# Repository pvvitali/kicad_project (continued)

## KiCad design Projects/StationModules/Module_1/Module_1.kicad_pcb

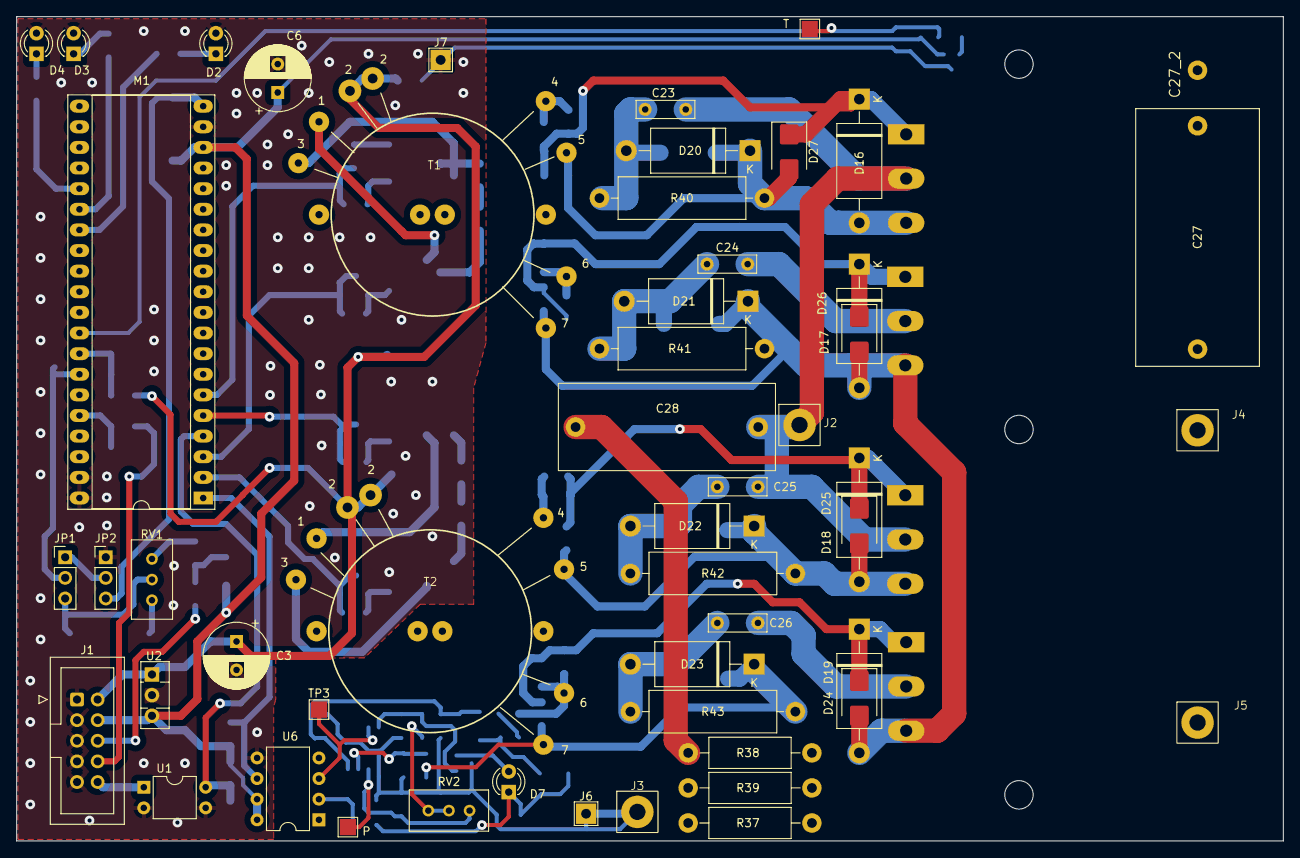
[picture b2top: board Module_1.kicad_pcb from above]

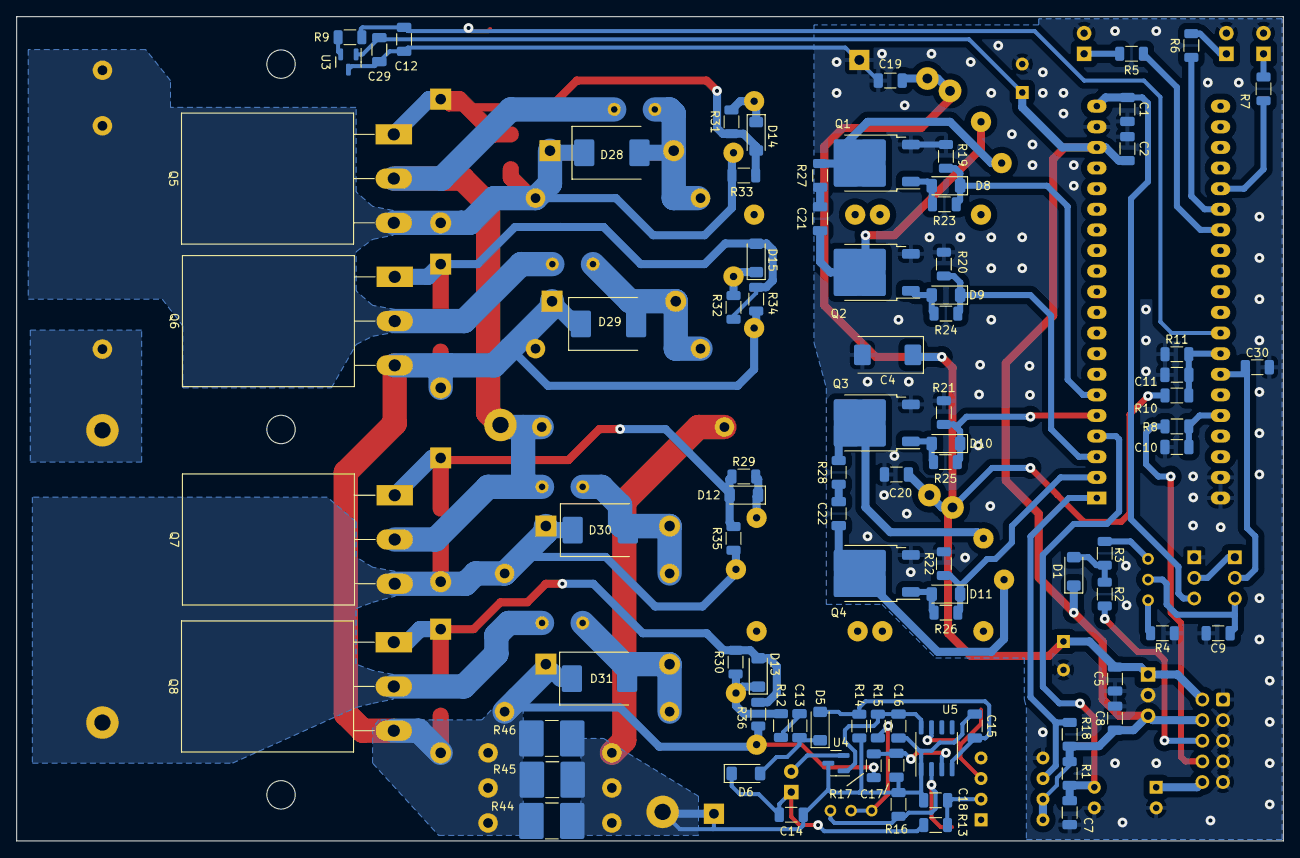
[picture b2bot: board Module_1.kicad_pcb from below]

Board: 2 copper layers, 156.0 x 101.5 mm, 142 parts (87 on the bottom side), 68 nets.

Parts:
C1, C2, C5, C7, C8, C11, C12, C16, C18, C29, C30: 0,1uF; C_1206_3216Metric
C3, C6: 470uF 25V; CP_Radial_D8.0mm_P3.50mm
C4: 100uF; CP_EIA-7343-15_Kemet-W
C9, C10: 10nF; C_1206_3216Metric
C13, C14, C15: 0,33uF; C_1206_3216Metric
C17: 2,2n; C_1206_3216Metric
C19, C20: 0,47uF; C_1206_3216Metric
C21, C22: 1n; C_1206_3216Metric
C23, C24, C25, C26: 1n 630v; C_Rect_L7.0mm_W2.0mm_P5.00mm
C27: 2u 600V; C_Rect_L31.5mm_W15.0mm_P27.50mm_MKS4
C27_2: (no value)
C28: 0,47u 600V; C_Rect_L26.5mm_W10.5mm_P22.50mm_MKS4
D1, D5, D6, D8, D9, D10, D11, D12, D13, D14, D15: LL4148; D_MiniMELF
D2, D3, D4, D7: LED_D3.0mm
D16, D17, D18, D19: P6KE18CA; D_DO-201AE_P15.24mm_Horizontal
D20, D21, D22, D23: UF5408; D_DO-201AE_P15.24mm_Horizontal
D24, D25, D26, D27: SMBJ18CA; D_SMB
D28, D29, D30, D31: ES3JC; D_SMC
H1, H2, H3: MountingHole; MountingHole_3.5mm
J1: IDC-Header_2x05_P2.54mm_Vertical
J2: +310; PinD2mm
J3: -310; PinD2mm
J4: PowerTrans1; PinD2mm
J5: PowerTrans2; PinD2mm
J6: -310V; TestPoint_THTPad_2.5x2.5mm_Drill1.2mm
J7: -12V; TestPoint_THTPad_2.5x2.5mm_Drill1.2mm
JP1, JP2: Jumper_3_Open; PinHeader_1x03_P2.54mm_Vertical
M1: BluePillStm32; DIP-40_W15.24mm_Socket_LongPads
P: TestPoint; TestPoint_Pad_2.0x2.0mm
Q1, Q2, Q3, Q4: STD20NF06T4; TO-252-2
Q5, Q6, Q7, Q8: STW20NM60; TO-247-3_Horizontal_TabUp
R1, R3, R4, R9, R11, R15: 4,7k; R_1206_3216Metric
R2: 470; R_1206_3216Metric
R5, R6, R7, R13, R27, R28: 330; R_1206_3216Metric
R8: 100; R_1206_3216Metric
R10: 15k; R_1206_3216Metric
R12: 680; R_1206_3216Metric
R14, R18: 1,5k; R_1206_3216Metric
R16: 150; R_1206_3216Metric
R17: 1k; R_1206_3216Metric
R19, R20, R21, R22: 3,3k; R_1206_3216Metric
R23, R24, R25, R26, R29, R30, R31, R32: 75; R_1206_3216Metric
R33, R34, R35, R36: 2,2k; R_1206_3216Metric
R37, R38, R39: 0,01; R_Axial_DIN0411_L9.9mm_D3.6mm_P15.24mm_Horizontal
R40, R41, R42, R43: 18; R_Axial_DIN0516_L15.5mm_D5.0mm_P20.32mm_Horizontal
R44, R45, R46: 0,01; R_2816_7142Metric
RV1, RV2: 5k; Potentiometer_Bourns_3296W_Vertical
T: TestPoint; TestPoint_Pad_2.0x2.0mm
T1, T2: Transformer_SP_2S; Trans_SP_2S
TP3: TestPoint; TestPoint_Pad_2.0x2.0mm
U1: PC817; DIP-4_W7.62mm
U2: L7805; TO-126-3_Vertical
U3: TC1047AxNB; SOT-23
U4: 78L05S; SOT-23
U5: LM311; SO-8_3.9x4.9mm_P1.27mm
U6: 6N137; DIP-8_W7.62mm

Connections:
+3V3: C1.1, JP2.3 (B), M1.20 (3V3)
+5V: C2.1, C6.1, C8.1, C29.1, D1.1 (K), J1.4, M1.18 (5V), R1.2, R18.2, U2.3 (OUT), U3.1 (V_{DD}), U6.7 (EN), U6.8 (VCC)
+12V: C3.1, C4.1, C5.1, C19.2, C20.2, J1.2, R10.2, T1.2 (PM), T2.2 (PM), U2.1 (IN)
/DriverFet/Driver_A: Q1.2 (D), R27.2, T1.3 (IN-)
/DriverFet/Driver_AN: C21.2, Q2.2 (D), T1.1 (IN+)
/DriverFet/Driver_B: Q3.2 (D), R28.2, T2.1 (IN+)
/DriverFet/Driver_BN: C22.2, Q4.2 (D), T2.3 (IN-)
/IN1: J1.10, U1.1
/IN_1: C7.1, M1.4 (PB15/SPI2_MOSI), R1.1, U1.4
/I_ER: M1.1 (PB12/SPI2_NSS), R18.1, U6.6 (VO)
/LED1: M1.25 (PA0), R7.1
/LED2: M1.26 (PA1), R6.1
/LED3: M1.27 (PA2/USART2_TX), R5.1
/OS: C30.1, JP1.2 (C), M1.34 (PB1)
/OS_IN: J1.6, R2.1
/OUTI1: J1.8, R8.1
/OUT_1: C10.1, M1.36 (PB11/USART3_RX), R8.2
/PWM_A: D8.1 (K), M1.6 (PA9/USART1_TX), R19.2, R23.2
/PWM_AN: D9.1 (K), M1.3 (PB14/SPI2_MISO), R20.1, R24.2
/PWM_B: D10.1 (K), M1.5 (PA8), R21.2, R25.2
/PWM_BN: D11.1 (K), M1.2 (PB13/SPI2_SCK), R22.1, R26.2
/Shunt+: D17.2 (A2), D19.2 (A2), D21.1 (A1), D23.1 (A1), D24.2 (A2), D26.2 (A2), D29.1 (K), D31.1 (K), Q6.3 (S), Q8.3 (S), R17.2, R34.1, R36.1, R37.1, R38.1, R39.1, R41.2, R43.2, R44.1, R45.1, R46.1, T1.7 (OUT2B), T2.7 (OUT2B)
/Shunt-: C14.2, C15.1, C16.2, C17.2, C18.2, C28.2, J3.1, J6.1, R14.2, R16.1, R37.2, R38.2, R39.2, R44.2, R45.2, R46.2, U4.3 (GND), U5.1 (GND)
/TMP: C12.1, M1.32 (PA7/SPI_MOSI), R9.2, T.1
/Transf_out: D13.1 (K), R12.2, R30.2, T2.6 (OUT2A)
/UP: C11.1, M1.33 (PB0), R10.1, R11.2
GND: C1.2, C2.2, C3.2, C4.2, C5.2, C6.2, C7.2, C8.2, C9.2, C10.2, C11.2, C12.2, C19.1, C20.1, C29.2, C30.2, D2.2 (K), D3.2 (K), D4.2 (K), J1.1, J1.3, J1.5, J1.7, J1.9, J7.1, JP2.1 (A), M1.19 (GND), M1.39 (GND), M1.40 (GND), Q1.3 (S), Q2.3 (S), Q3.3 (S), Q4.3 (S), R4.1, R11.1, R19.1, R20.2, R21.1, R22.2, U1.2, U1.3, U2.2 (GND), U3.3 (GND), U6.5 (GND)
unnamed: C13.1, R12.1
unnamed: C21.1, R27.1
unnamed: C22.1, R28.1
unnamed: D1.2 (A), R2.2, R3.1
unnamed: D2.1 (A), R5.2
unnamed: D3.1 (A), R6.2
unnamed: D4.1 (A), R7.2
unnamed: C15.2, D5.2 (A), R14.1, U5.4 (V-)
unnamed: C13.2, D5.1 (K), D6.2 (A)
unnamed: C14.1, D6.1 (K), D7.1 (A), R13.1
unnamed: D7.2 (K), U4.2 (IN)
unnamed: D8.2 (A), Q1.1 (G), R23.1
unnamed: D9.2 (A), Q2.1 (G), R24.1
unnamed: D10.2 (A), Q3.1 (G), R25.1
unnamed: D11.2 (A), Q4.1 (G), R26.1
unnamed: D12.2 (A), D18.1 (A1), D25.1 (A1), Q7.1 (G), R29.1, R35.2
unnamed: D12.1 (K), R29.2, T2.4 (OUT1A)
unnamed: D13.2 (A), D19.1 (A1), D24.1 (A1), Q8.1 (G), R30.1, R36.2
unnamed: D14.2 (A), D16.1 (A1), D27.1 (A1), Q5.1 (G), R31.1, R33.2
unnamed: D14.1 (K), R31.2, T1.4 (OUT1A)
unnamed: D15.2 (A), D17.1 (A1), D26.1 (A1), Q6.1 (G), R32.1, R34.2
unnamed: D15.1 (K), R32.2, T1.6 (OUT2A)
unnamed: C24.1, C27.1, C27_2.1, D16.2 (A2), D20.1 (A1), D27.2 (A2), D28.1 (K), Q5.3 (S), Q6.2 (D), R33.1, R40.2, T1.5 (OUT1B)
unnamed: C26.1, D18.2 (A2), D22.1 (A1), D25.2 (A2), D30.1 (K), J5.1, Q7.3 (S), Q8.2 (D), R35.1, R42.2, T2.5 (OUT1B)
unnamed: C23.2, D20.2 (A2), D28.2 (A), R40.1
unnamed: C24.2, D21.2 (A2), D29.2 (A), R41.1
unnamed: C25.2, D22.2 (A2), D30.2 (A), R42.1
unnamed: C26.2, D23.2 (A2), D31.2 (A), R43.1
unnamed: C23.1, C25.1, C28.1, J2.1, Q5.2 (D), Q7.2 (D)
unnamed: C27.2, J4.1
unnamed: JP1.1 (A), JP2.2 (C)
unnamed: C9.1, JP1.3 (B), RV1.2
unnamed: R3.2, RV1.1
unnamed: R4.2, RV1.3
unnamed: R15.1, RV2.1, RV2.2
unnamed: R9.1, U3.2 (V_{OUT})
unnamed: C16.1, R15.2, U4.1 (OUT), U5.8 (V+)
unnamed: P.1, R16.2, RV2.3, U5.2 (+)
unnamed: C17.1, R17.1, U5.3 (-)
unnamed: C18.1, R13.2, U6.2 (A)
unnamed: TP3.1, U5.7, U6.3 (C)

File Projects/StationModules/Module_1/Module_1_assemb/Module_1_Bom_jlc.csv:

Reference,Value,Footprint,Description,LCSC,MFR.Part,Mounting,Qty
"C1, C2, C5, C7, C8, C11, C12, C16, C18, C29, C30","0,1uF",Capacitor_SMD:C_1206_3216Metric,50V 100nF X7R ±10% 1206 Multilayer Ceramic Capacitors MLCC - SMD/SMT ROHS,C82601,CC1206KRX7R9BB104,Yes,11
"C3, C6",470uF 25V,Capacitor_THT:CP_Radial_D8.0mm_P3.50mm,"470uF 25V ±20% 440mA@120Hz Plugin,D8xL11.5mm Aluminum Electrolytic Capacitors - Leaded ROHS",C88730,25PX470MEFC8X11.5,Yes,2
C4,100uF,Capacitor_Tantalum_SMD:CP_EIA-7343-15_Kemet-W,100uF 20V 900mΩ@100kHz ±10% CASE-D-7343 Tantalum Capacitors ROHS,C122302,T491D107K020AT,Yes,1
"C9, C10",10nF,Capacitor_SMD:C_1206_3216Metric,1kV 10nF X7R ±10% 1206 Multilayer Ceramic Capacitors MLCC - SMD/SMT ROHS,C9194,1206B103K102NT,Yes,2
"C13, C14, C15","0,33uF",Capacitor_SMD:C_1206_3216Metric,50V 330nF X7R ±10% 1206 Multilayer Ceramic Capacitors MLCC - SMD/SMT ROH,C274377,CC1206KRX7R9BB334,Yes,3
"C17, C21, C22",1n,Capacitor_SMD:C_1206_3216Metric,50V 1nF NP0 ±2% 1206 Multilayer Ceramic Capacitors MLCC - SMD/SMT ROHS,C527247,CC1206GRNPO9BN102,Yes,3
"C19, C20","0,47uF",Capacitor_SMD:C_1206_3216Metric,50V 470nF X7R ±10% 1206 Multilayer Ceramic Capacitors MLCC - SMD/SMT ROHS,C107182,C107182,Yes,2
"C23, C24, C25, C26",1n 630v,Capacitor_THT:C_Rect_L7.0mm_W2.0mm_P5.00mm,"±5% 630V 1nF PET Plugin,P=5mm Film Capacitors ROHS",C914547,CL11-2J102J-630V,Yes,4
C27,2u 600V,Capacitor_THT:C_Rect_L31.5mm_W15.0mm_P27.50mm_MKS4,"2uF ±10% 600V Plugin,P=27.5mm Polypropylene Film Capacitors (CBB) ROHS",C330414,C3D1U205KB00C00,Yes,1
C28,"0,47u 600V",Capacitor_THT:C_Rect_L26.5mm_W10.5mm_P22.50mm_MKS4,"470nF ±5% 750V Plugin,P=20mm Polypropylene Film Capacitors (CBB) ROHS",C2803198,C2803198,Yes,1
"D1, D5, D6, D8, D9, D10, D11, D12, D13, D14, D15",LL4148,Diode_SMD:D_MiniMELF,75V 500mW 1V@10mA 4ns 150mA LL-34 Switching Diode ROHS,C2891733,LL4148,Yes,11
D2,,LED_THT:LED_D3.0mm,"619nm Red 60° Plugin,P=2.54mm Light Emitting Diodes (LED) ROHS",C99771,TLHR5400,Yes,1
D3,,LED_THT:LED_D3.0mm,588nm~588nm yellow 60° Plugin Light Emitting Diodes (LED) ROHS,C779430,TZ-L2-03YYBY2YDJ30-001,Yes,1
"D4, D7",,LED_THT:LED_D3.0mm,"green Plugin,D=3.2mm Light Emitting Diodes (LED) ROHS",C2895476,TLHG4400,Yes,2
"D24, D25, D26, D27",SMBJ18CA,Diode_SMD:D_SMB,18V 20V 29.2V SMB(DO-214AA) TVS ROHS,C440286,SMBJ18CA,Yes,4
"D28, D29, D30, D31",ES3JC,Diode_SMD:D_SMC,1.65V 35ns Single 3A 600V SMC(DO-214AB) Diodes - Fast Recovery Rectifiers ROHS,C2936068,ES3JC,Yes,4
J1,,Connector_IDC:IDC-Header_2x05_P2.54mm_Vertical,"2.54mm Straight 2x5P 5 Push - Pull 2.54mm 2 Plugin,P=2.54mm IDC Connectors ROHS",C5665,C5665,Yes,1
"JP1, JP2",Jumper_3_Open,Connector_PinHeader_2.54mm:PinHeader_1x03_P2.54mm_Vertical,"Gold 250V 3A Straight Square Pins 2.54mm 3P 260℃ 6mm -40℃~+105℃ 3mm 2.54mm Brass Black Plugin 2.54mm 1x3P Plugin,P=2.54mm Pin Headers ROHS",C49257,HB-PH3-25413PB2GOP,Yes,2
"Q1, Q2, Q3, Q4",STD20NF06T4,Package_TO_SOT_SMD:TO-252-2,"30A 35mΩ@15A,10V 55W TO-252 MOSFETs ROHS",C668203,STD20NF06L,Yes,4
"R1, R3, R4, R9, R11, R15","4,7k",Resistor_SMD:R_1206_3216Metric,250mW Thick Film Resistors ±100ppm/℃ ±5% 4.7kΩ 1206 Chip Resistor - Surface Mount ROHS,C136458,RC1206JR-074K7L,Yes,6
R2,470,Resistor_SMD:R_1206_3216Metric,250mW Thick Film Resistors ±100ppm/℃ ±5% 470Ω 1206 Chip Resistor - Surface Mount ROHS,C114945,RC1206FR-07470RL,Yes,1
"R5, R6, R7, R13, R27, R28",330,Resistor_SMD:R_1206_3216Metric,250mW Thick Film Resistors ±100ppm/℃ ±5% 330Ω 1206 Chip Resistor - Surface Mount ROH,C137152,RC1206JR-07330RL,Yes,6
R8,100,Resistor_SMD:R_1206_3216Metric,250mW Thick Film Resistors ±100ppm/℃ ±5% 100Ω 1206 Chip Resistor - Surface Mount ROHS,C113307,RC1206JR-07100RL,Yes,1
R10,15k,Resistor_SMD:R_1206_3216Metric,250mW Thick Film Resistors ±100ppm/℃ ±5% 15kΩ 1206 Chip Resistor - Surface Mount ROHS,C137199,RC1206JR-0715KL,Yes,1
R12,680,Resistor_SMD:R_1206_3216Metric,250mW Thick Film Resistors ±100ppm/℃ ±5% 680Ω 1206 Chip Resistor - Surface Mount ROHS,C25392,1206W4J0681T5E,Yes,1
"R14, R18","1,5k",Resistor_SMD:R_1206_3216Metric,250mW Thick Film Resistors ±100ppm/℃ ±5% 1.5kΩ 1206 Chip Resistor - Surface Mount ROHS,C137189,RC1206JR-071K5L,Yes,2
R16,150,Resistor_SMD:R_1206_3216Metric,250mW Thick Film Resistors ±100ppm/℃ ±5% 150Ω 1206 Chip Resistor - Surface Mount ROHS,C25353,1206W4J0151T5E,Yes,1
R17,1k,Resistor_SMD:R_1206_3216Metric,250mW Thick Film Resistors ±1% 1kΩ 1206 Chip Resistor - Surface Mount ROHS,C4410,1206W4F1001T5E,Yes,1
"R19, R20, R21, R22","3,3k",Resistor_SMD:R_1206_3216Metric,250mW Thick Film Resistors ±100ppm/℃ ±5% 3.3kΩ 1206 Chip Resistor - Surface Mount ROHS,C26041,1206W4J0332T5E,Yes,4
"R23, R24, R25, R26, R29, R30, R31, R32",75,Resistor_SMD:R_1206_3216Metric,250mW Thick Film Resistors ±100ppm/℃ ±1% 75Ω 1206 Chip Resistor - Surface Mount ROHS,C17987,1206W4F750JT5E,Yes,8
"R33, R34, R35, R36","2,2k",Resistor_SMD:R_1206_3216Metric,250mW Thick Film Resistors ±100ppm/℃ ±5% 2.2kΩ 1206 Chip Resistor - Surface Mount ROHS,C137167,RC1206JR-072K2L,Yes,4
"R40, R41, R42, R43",18,Resistor_THT:R_Axial_DIN0516_L15.5mm_D5.0mm_P20.32mm_Horizontal,"18Ω 2W ±350ppm/℃ ±5% Plugin,5x15.5mm Through Hole Resistors ROHS",C119690,CR2W-18Ω±5%-9T73,Yes,4
"R44, R45, R46","0,01",Resistor_SMD:R_2816_7142Metric,2W ±75ppm/℃ ±1% 10mΩ 2816 Chip Resistor - Surface Mount ROHS,C511405,WSHM2818R0100FEA,Yes,3
"RV1, RV2",5k,Potentiometer_THT:Potentiometer_Bourns_3296W_Vertical,±10% 5kΩ Plugin Variable Resistors/Potentiometers ROHS,C118907,3296W-1-502,Yes,2
U1,PC817,Package_DIP:DIP-4_W7.62mm,"80V 5000V 50mA 0.1V@1mA,20mA 1 6V 1.2V DC DIP-4 Optocouplers - Phototransistor Output ROHS",C2833074,PC817X2YSZW,Yes,1
U2,L7805,Package_TO_SOT_THT:TO-126-3_Vertical,68dB@(120Hz) 1.5A null 5V positive 35V TO-220 Linear Voltage Regulators (LDO) ROHS,C3795,L7805CV-DG,Yes,1
U3,TC1047AxNB,Package_TO_SOT_SMD:SOT-23,SOT-23(TO-236) Temperature Sensors ROHS,C50052,TC1047AVNBTR,Yes,1
U4,78L05S,Package_TO_SOT_SMD:SOT-23,100mA Fixed 5V Positive 30V SOT-23 Linear Voltage Regulators (LDO) ROHS,C2858514,78L05S,Yes,1
U5,LM311,Package_SO:SO-8_3.9x4.9mm_P1.27mm,7.5mV 0.25uA SO-8 Comparators ROHS,C2868397,LM311PSR,Yes,1
U6,6N137,Package_DIP:DIP-8_W7.62mm,10Mbit/s 75ns 7V 5kV/us DC DIP-8 Optocouplers - Logic Output ROHS,C142297,6N137,Yes,1

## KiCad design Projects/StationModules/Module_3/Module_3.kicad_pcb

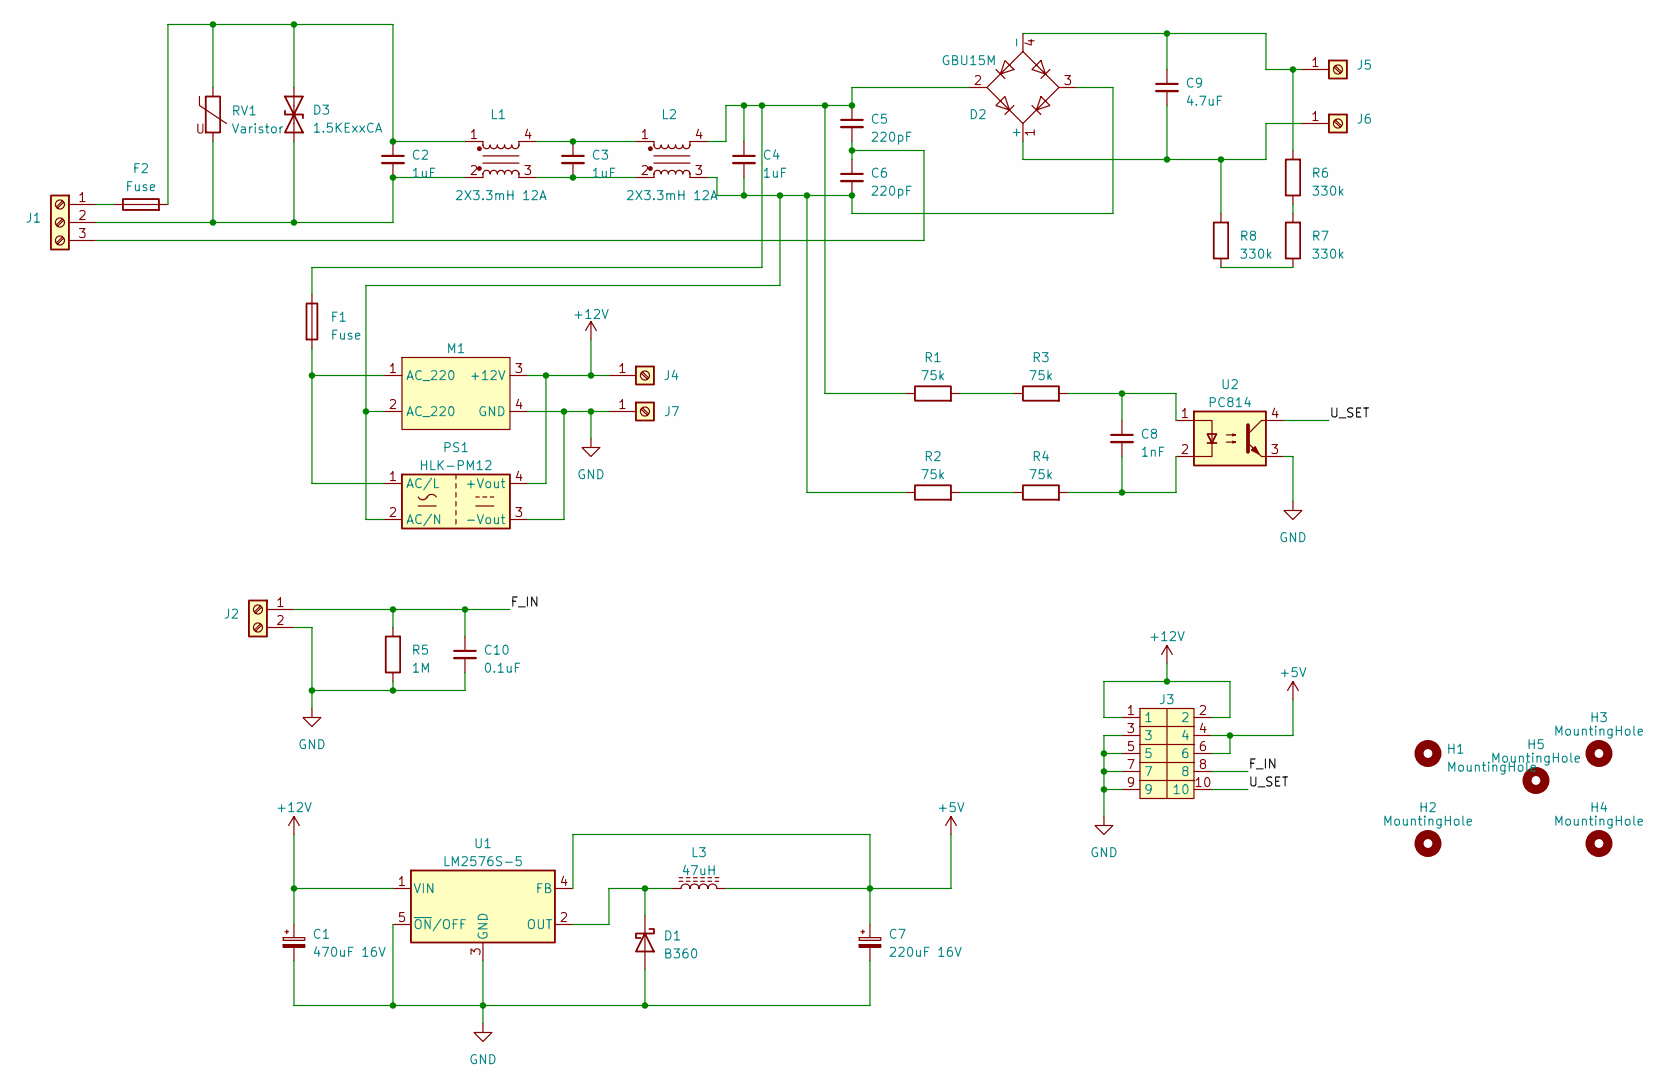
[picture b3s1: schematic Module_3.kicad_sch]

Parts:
C1: 470uF 16V; CP_Radial_D8.0mm_P3.50mm; MFR.Part 16YXJ470M8X11.5; LCSC C432444
C2, C3, C4: 1uF; C_Rect_L18.0mm_W11.0mm_P15.00mm_FKS3_FKP3; MFR.Part MPX105K31D5KN15800; LCSC C504224
C5, C6: 220pF; C_Disc_D9.0mm_W5.0mm_P7.50mm; MFR.Part S07B1E221KN0B0S0N0; LCSC C249173
C7: 220uF 16V; CP_Radial_D8.0mm_P3.50mm; MFR.Part 16YXF220MFFC8X11.5; LCSC C334323
C8: 1nF; C_1206_3216Metric; MFR.Part CC1206KKX7RDBB102; LCSC C23631
C9: 4.7uF; C_Rect_L29.0mm_W11.0mm_P27.50mm_MKT; MFR.Part KP475J2J2603; LCSC C3019080
C10: 0.1uF; C_1206_3216Metric; MFR.Part CC1206KKX7RDBB102; LCSC C23631
D1: B360; D_SMC; MFR.Part B360-13-F; LCSC C110487
D2: GBU15M; Diode_Bridge_Vishay_GBU; MFR.Part GBU15M; LCSC C970324
D3: 1.5KExxCA; D_DO-201AE_P15.24mm_Horizontal; MFR.Part 1.5KE400CA; LCSC C720189
F1: Fuse; Fuse_Littelfuse_395Series; MFR.Part 2010T1A250V; LCSC C354900
F2: Fuse; R_Axial_Power_L20.0mm_W6.4mm_P25.40mm; MFR.Part 0218010.MXEP; LCSC C142774
H1, H2, H3, H4, H5: MountingHole; MountingHole_3.2mm_M3
J1: Screw_Terminal_01x03; DB129V-7.62-3P-GN-S; MFR.Part DB129V-7.62-3P-GN-S; LCSC C395859
J2: Screw_Terminal_01x02; DB129V-7.62-2P-GN-S; MFR.Part DB129V-7.62-2P-GN-S; LCSC C395858
J3: IDC-Header_2x05_P2.54mm_Vertical; MFR.Part C5665; LCSC C5665
J4, J7: Screw_Terminal_01x01; PinD1_6mm
J5, J6: Screw_Terminal_01x01; PinD3mm
L1, L2: 2X3.3mH 12A; FilterSetevoy_20x30_p20; MFR.Part B82726S6123N020; LCSC B82726S6123N020
L3: 47uH; L_12x12mm_H8mm; MFR.Part MBH125-470M; LCSC C2981394
M1: AC_DC_12V2A
PS1: HLK-PM12; Converter_ACDC_HiLink_HLK-5Mxx; MFR.Part HLK-5M12; LCSC C209908
R1, R2, R3, R4: 75k; R_1206_3216Metric; MFR.Part RC1206FR-0775KL; LCSC C137234
R5: 1M; R_1206_3216Metric; MFR.Part 1206W4F1004T5E; LCSC C17927
R6, R7, R8: 330k; R_1206_3216Metric; MFR.Part AC1206FR-07330KL; LCSC C144497
RV1: Varistor; RV_Disc_D21.5mm_W4.3mm_P10mm; MFR.Part VDR-20D391K; LCSC C6793796
U1: LM2576S-5; TO-263-5_TabPin3; MFR.Part LM2576S-5; LCSC C347413
U2: PC814; DIP-4_W7.62mm; MFR.Part LTV-814-B; LCSC C7435550

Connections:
+5V: C7.1, J3.4, J3.6, L3.2, U1.4 (FB)
+12V: C1.1, J3.1, J3.2, J4.1, M1.3 (+12V), PS1.4 (+Vout), U1.1 (VIN)
/F_IN: C10.1, J2.1, J3.8, R5.2
/U_SET: J3.10, U2.4
GND: C1.2, C7.2, C10.2, D1.2 (A), J2.2, J3.3, J3.5, J3.7, J3.9, J7.1, M1.4 (GND), PS1.3 (-Vout), R5.1, U1.3 (GND), U1.5 (~ON/OFF), U2.3
unnamed: C3.1, L1.4, L2.1
unnamed: C3.2, L1.3, L2.2
unnamed: C4.1, C5.1, D2.2, F1.1, L2.4, R1.1
unnamed: C8.1, R3.2, U2.1
unnamed: C8.2, R4.2, U2.2
unnamed: D1.1 (K), L3.1, U1.2 (OUT)
unnamed: C9.2, D2.1 (+), J6.1, R8.2
unnamed: C9.1, D2.4 (-), J5.1, R6.2
unnamed: C2.1, D3.1 (A1), F2.2, L1.1, RV1.1
unnamed: C2.2, D3.2 (A2), J1.2, L1.2, RV1.2
unnamed: F2.1, J1.1
unnamed: C5.2, C6.1, J1.3
unnamed: F1.2, M1.1 (AC_220), PS1.1 (AC/L)
unnamed: C4.2, C6.2, D2.3, L2.3, M1.2 (AC_220), PS1.2 (AC/N), R2.1
unnamed: R1.2, R3.1
unnamed: R2.2, R4.1
unnamed: R6.1, R7.2
unnamed: R7.1, R8.1

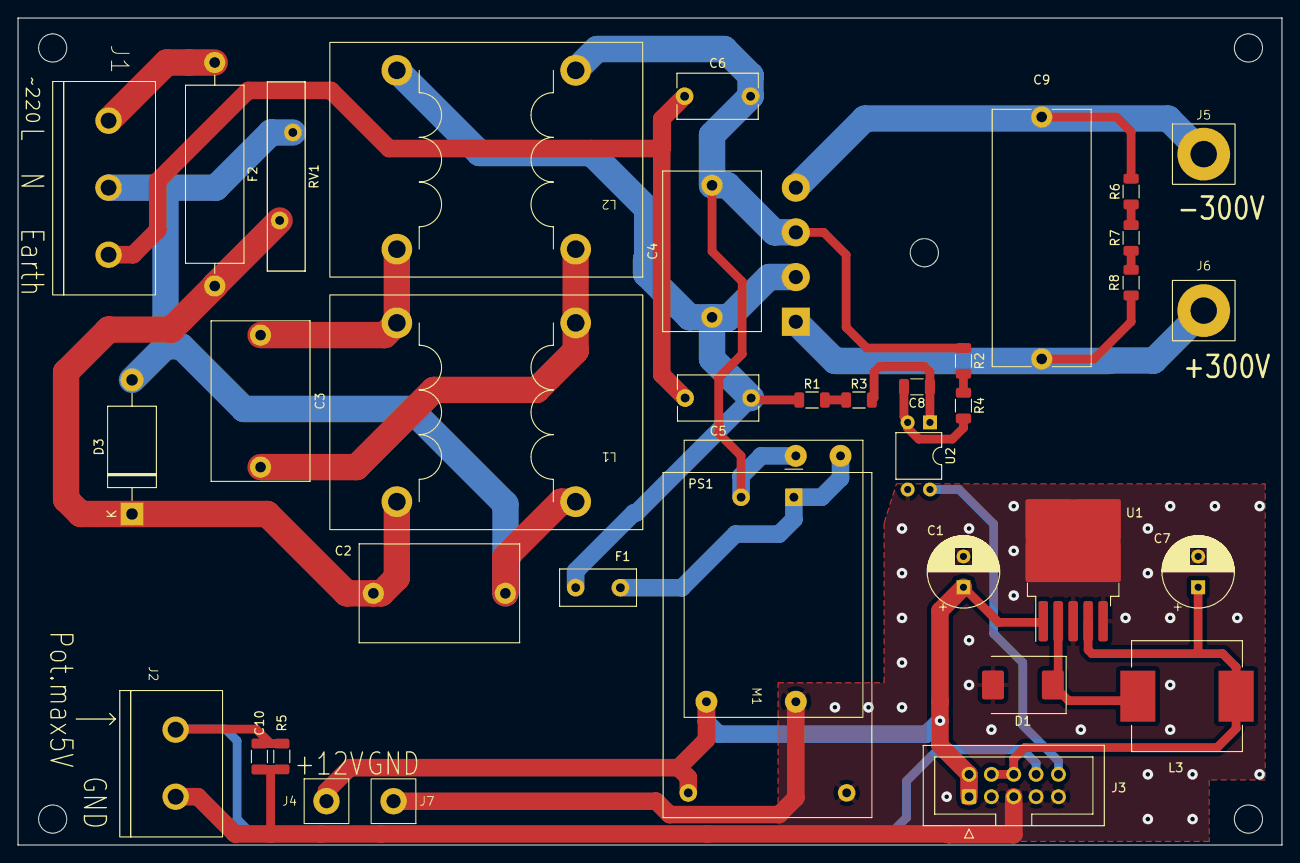
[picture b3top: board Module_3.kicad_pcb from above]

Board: 2 copper layers, 143.6 x 94.0 mm, 43 parts (1 on the bottom side), 23 nets.

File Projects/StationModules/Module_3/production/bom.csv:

Designator,Footprint,Quantity,Value,LCSC Part #
C1,CP_Radial_D8.0mm_P3.50mm,1,470uF 16V,C432444
"C2, C3, C4",C_Rect_L24.0mm_W10.9mm_P22.50mm_MKT,3,470nF,C518924
"C5, C6",C_Disc_D9.0mm_W5.0mm_P7.50mm,2,220pF,C2914701
C7,CP_Radial_D8.0mm_P3.50mm,1,220uF 16V,C159828
C8,1206,1,1nF,
C9,C_Rect_L29.0mm_W11.0mm_P27.50mm_MKT,1,4.7uF,C2846750
D1,D_SMC,1,B360,C110487
D2,Diode_Bridge_Vishay_GBU,1,GBU15M,C970324
F1,Fuseholder_Clip-5x20mm_Keystone_3517_Inline_P23.11x6.76mm_D1.70mm_Horizontal,1,Fuse,C3029536 2pts
"H1, H2, H3, H4, H5",MountingHole_3.2mm_M3,5,MountingHole,
J1,DB129V-7.62-3P-GN-S,1,Screw_Terminal_01x03,C395859
J2,DB129V-7.62-2P-GN-S,1,Screw_Terminal_01x02,C395858
J3,IDC-Header_2x05_P2.54mm_Vertical,1,~,
"J4, J7",PinD1_6mm,2,Screw_Terminal_01x01,
"J5, J6",PinD4mm,2,Screw_Terminal_01x01,
"L1, L2",B82726S6123N020,2,2X3.3mH 12A,B82726S6123N020
L3,L_12x12mm_H8mm,1,47uH,C2981394
M1,AC_DC_12V2A,1,~,
"R1, R2, R3, R4",1206,4,75k,
U1,TO-263-5_TabPin3,1,LM2576S-5,C880552
U2,DIP-4_W7.62mm,1,PC814,

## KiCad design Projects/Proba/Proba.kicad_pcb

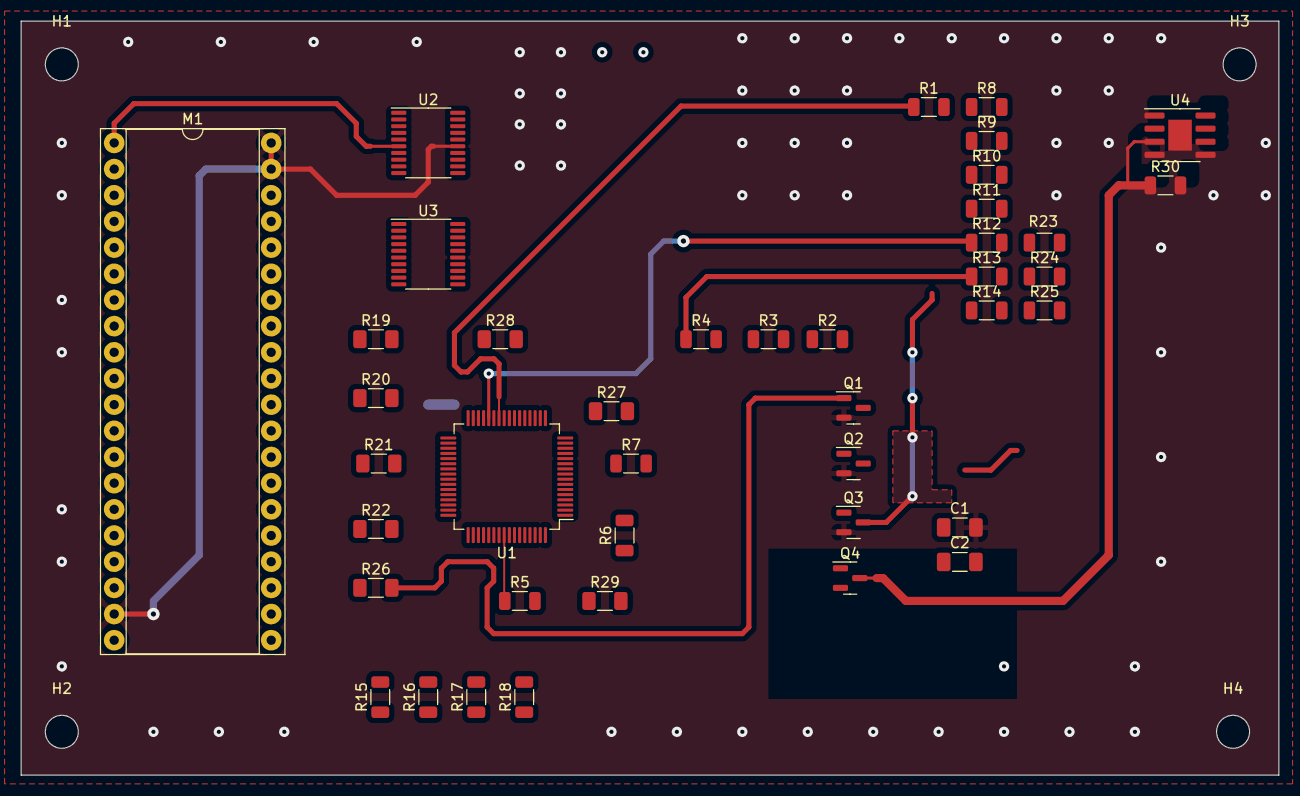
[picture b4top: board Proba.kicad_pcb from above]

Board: 2 copper layers, 122.1 x 73.2 mm, 45 parts (0 on the bottom side), 40 nets.

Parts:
C1: 10n; C_1206_3216Metric_Pad1.33x1.80mm_HandSolder
C2: 4n7; C_1206_3216Metric_Pad1.33x1.80mm_HandSolder
H1, H2, H3, H4: MountingHole; MountingHole_3.2mm_M3
M1: BluePillStm32; DIP-40_W15.24mm_Socket
Q1, Q2, Q3, Q4: AO3400A; SOT-23
R1, R2, R3, R4, R5, R6, R7, R8, R9, R10, R11, R12, R13, R14, R15, R16, R17, R18, R23, R24, R25, R30: R; R_1206_3216Metric
R19, R20, R21, R22, R26, R27, R28: 10k; R_1206_3216Metric_Pad1.30x1.75mm_HandSolder
R29: 100; R_1206_3216Metric_Pad1.30x1.75mm_HandSolder
U1: STM32F103R6Tx; LQFP-64_10x10mm_P0.5mm
U2, U3: STM32F030F4Px; TSSOP-20_4.4x6.5mm_P0.65mm
U4: LM358; SOIC-8-1EP_3.9x4.9mm_P1.27mm_EP2.29x3mm

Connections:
+3.3V: U1.1 (VBAT), U1.19 (VDD), U1.32 (VDD), U1.48 (VDD), U1.64 (VDD), U2.5 (VDDA), U2.16 (VDD), U3.5 (VDDA), U3.16 (VDD), U4.8 (V+)
/PA0: M1.1 (PB12/SPI2_NSS), R1.2, U2.6 (PA0), U3.6 (PA0)
/PA1: R2.2, U2.7 (PA1), U3.7 (PA1)
/PA2: R3.2, U2.8 (PA2), U3.8 (PA2)
/PA3: R4.2, U1.17 (PA3), U2.9 (PA3), U3.9 (PA3)
/PA4: R5.2, U1.20 (PA4), U2.10 (PA4), U3.10 (PA4)
/PA5: R6.2, U1.21 (PA5), U2.11 (PA5), U3.11 (PA5)
/PA6: R7.2, U1.22 (PA6), U2.12 (PA6), U3.12 (PA6)
/PA7: R8.2, U1.23 (PA7), U2.13 (PA7), U3.13 (PA7)
/PA8: R9.2, U1.41 (PA8), U2.17 (PA9), U3.17 (PA9)
/PA9: U1.42 (PA9), U2.18 (PA10), U3.18 (PA10)
/PA10: U1.43 (PA10), U2.19 (PA13), U3.19 (PA13)
/PA11: U2.20 (PA14), U3.20 (PA14)
/PB0: R1.1, R10.1, U1.26 (PB0)
/PB1: R2.1, R11.1, U1.27 (PB1)
/PB2: R3.1, R12.1, U1.28 (PB2)
/PB3: R4.1, R13.1, U1.55 (PB3)
/PB4: R5.1, R14.1, U1.56 (PB4)
/PB5: R6.1, R15.1, U1.57 (PB5)
/PB6: R7.1, R16.1, U1.58 (PB6)
/PB7: R8.1, R17.1, U1.59 (PB7)
/PB8: R9.1, R18.1, U1.61 (PB8)
/PC2: R20.1, U1.10 (PC2)
/PC3: R21.1, U1.11 (PC3)
/in1: Q4.3 (D), R30.1, U4.3 (+)
/in2: Q3.3 (D), R30.2, U4.2 (-)
/slc: R19.1, U1.9 (PC1)
CLOCK: R19.2, U1.4 (PC15)
GND: C1.2, C2.2, M1.19 (GND), M1.39 (GND), M1.40 (GND), Q1.2 (S), Q2.2 (S), Q3.2 (S), Q4.2 (S), U1.12 (VSSA), U1.18 (VSS), U1.31 (VSS), U1.47 (VSS), U1.63 (VSS), U2.15 (VSS), U3.15 (VSS), U4.4 (V-)
unnamed: Q1.1 (G), R26.2
unnamed: Q2.1 (G), R27.2
unnamed: C1.1, Q3.1 (G), R28.2
unnamed: C2.1, Q4.1 (G), R29.2
unnamed: R10.2, R23.1
unnamed: R11.2, R24.1
unnamed: R12.2, R25.1
unnamed: R26.1, U1.14 (PA0)
unnamed: R27.1, U1.15 (PA1)
unnamed: R28.1, U1.16 (PA2)
unnamed: R29.1, U1.45 (PA12)

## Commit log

2023-05-21 Place elements 1
2023-05-22 Place elements 2
2023-05-27 Trace complit 1
2023-05-29 Trace complit 2
2023-05-29 Trace complit 3
2023-05-30 Prod complit 1
2023-06-23 add sheme module 2
2023-06-24 sheet 2 Module 2
2023-06-30 module 2 pcb ver1
2023-07-03 module 2 board complit v1
2023-07-10 add module 3 route complit
2023-07-11 module 3, route complit 2
2023-07-21 add bom module 1
2023-07-25 add bom and pos
2023-09-28 finaly on summer
2023-09-28 change module1,2
2024-02-25 change on 25_02_24
2024-03-04 Corection all modules
2024-03-20 change for final 20.03.2024
